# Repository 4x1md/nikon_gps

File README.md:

# DIY GPS Module for Nikon DSLR

The Nikon GPS project is a compact and lightweight DIY module which adds GPS functionality to Nikon DSLR cameras. It adds the ability to record location data for each photo in the EXIF and later view it on a map.

The module is attached to the flash hot shoe mount and connects to the camera's dedicated GPS port. The GPS gets its power from the camera and transmits the received GPS NMEA sentences using UART at 4800 bps. It also features an on/off button and a LED indicator which shows when the GPS module is active.

The project was created mostly to advance my DIY and electronics skills.

## Overview

The idea of building a GPS for my Nikon DSLR me after building the [GPS module for my Yaesu VX-8DE transceiver](https://github.com/4x1md/vx8_gps). I searched the internet and found some projects, some of which had a very small size. For my project I chose RG1411 GPS module which is only 10x10mm in size. It requires 3.3V which can be supplied by the camera.

The first version of the GPS had a linear voltage regulator powering the GPS module. This solution had one big disadvantage: the GPS module was turned off completely and didn't keep any GPS data while it was off. Each time the module was turned on it had to acquire all the required GPS data again and consumed more current during the first minutes after power on. The delay of 3-5 minutes and even more made this GPS module impractical while walking in a city when I turned it on and off very often in order to save camera's battery.

The second version of this GPS project had the following changes:

1. The linear voltage regulator was replaced with a switching power supply with a very high efficiency at low currents.

2. On/off button puts the GPS module is a sleep mode instead of turning it off. In this mode it keeps the GPS data all the time when the GPS is connected to the camera and its start time is much shorter than during a full power-on cycle.

This document describes the latest version of this project. The first version of this project (revision A) is presented in [revision-a.md](docs/revision-a.md).

## Circuit Diagram

The project has the following circuits: GPS module, power supply, on/off switch, logic level shifter and LEDs. All the circuits are assembled on the same PCB.

1. **GPS module.** Hornet ORG1411 was chosen due to its small footprint and good performance. It is powered from the 3.3V supply and is connected in UART mode.

2. **Power supply.** TI TPS62203DBVR is a switching voltage regulator with fixed 3.3V output. It requires only an inductor and filter capacitors in order to work. It features more than 90% at the currents below 1mA. Such efficiency is important for reducing power consumption from the camera.

3. **On/off button.** The button is used to toggle the ON_OFF pin of the GPS for putting it into sleep mode or waking it up. The button is debounced by an RC-filter with a Schmitt trigger.

4. **Logic level shifter.** The logic level shifting circuit converts the 1.8V logic levels of the GPS to 3.3V levels required by the camera. When the GPS is in the sleep mode the level shifter enters high-Z mode. The enable pin of U3 is controlled by a circuit which acts like a flip-flop. If the WAKEUP pin of the GPS is LOW, the output of the AND gate U2 is also LOW and the output of U3 is disabled. After the GPS wakes up, its WAKEUP pin becomes HIGH, but the second input of U2 is still LOW, and its output continues LOW. When the UART TX of the GPS wakes up and becomes HIGH it toggles the output of U2 to HIGH. R5 pulls the B input of the AND gate up and the diode D1 prevents level of the B input from being changed to LOW by the UART RX when the latter transmits zero bits. The output of U2 will remain HIGH until the WAKEUP line falls to LOW again.

6. **LEDs.** The LEDs indicate that the GPS in in active state. They are controlled by the output of U2 and are turned off when the output buffer is in high-Z mode.

## Mechanics

The project is enclosed in a plastic box of 36x36x15mm. These boxes are cheap and are widely available on eBay/AliExpress.

## PCB Design

The PCB was designed in KiCAD. Its shape fits the plastic box shown above.

### 3D Model

### Manufactured PCB

## Assembled Device

## Device Tests

### Design Validation Tests

The tests were done in order to verify the assembled circuit. Refer to [development-tests-rev-b.md](docs/development-tests-rev-b.md) for test notes.

### ORG1411 GPS Module On/Off Tests

The on/off sequence of the ORG1411 GPS module was tested in order to understand how to connect an external on/off button to the module. Refer to [gps-on-off-tests.md](docs/gps-on-off-tests.md) for details.

### Field Tests

## Conclusions

The second version of the module works as I expected. I tested it in Tel Aviv, Budapest and Thessaloniki and it showed fast data acquisition and good precision. Currently, I'm not planning to develop it further.

## Links

### Reference projects

1. [A low-cost GPS module for Nikon DSLRs](https://github.com/marmat/nikon-gp1-diy) by Martin Matysiak
2. [Build Notes for DIY Nikon GPS](http://www.petermillerphoto.com/nikongps/nikongps2.html) by Peter Miller

### Technical data

1. [Nikon D90, D3100, D3200, D5000, D7000 focus / shutter MC-DC2 connector pinout](http://pinoutguide.com/DigitalCameras/nikon_d90_pinout.shtml)

## Questions? Suggestions?
You are more than welcome to contact me with any questions, suggestions or propositions regarding this project. You can:

1. Visit [my QRZ.COM page](https://www.qrz.com/db/4X5DM)
2. Visit [my Facebook profile](https://www.facebook.com/Dima.Meln)
3. Write me an email to iosaaris =at= gmail dot com

## How to Support or Say Thanks

If you like this project, or found here some useful information and want to say thanks, or encourage me to do more, you can buy me a coffee!

You can aslo make a donation with PayPal:

---

**73 de 4X1MD**

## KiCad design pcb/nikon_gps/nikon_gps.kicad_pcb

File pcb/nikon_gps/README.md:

# nikon_gps

This directory stores the latest version of the project. Currently, revision B of the PCB developped in KiCAD 5.1.

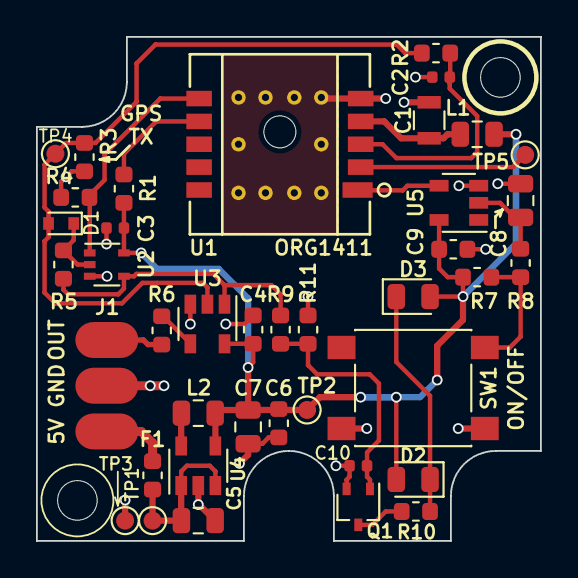
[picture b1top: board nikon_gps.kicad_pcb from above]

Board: 2 copper layers, 28.0 x 28.0 mm, 42 parts (0 on the bottom side), 21 nets.

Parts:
C1: 100nF; C_0805_NarrowPads
C2: 18pF; C_0402
C3, C10: 100nF; C_0402
C4, C9: 100nF; C_0603
C5: 4.7uF; C_0805
C6: 1nF; C_0603
C7: 10uF; C_0805
C8: 100nF; C_0805
D1: Shottky; D_SOD-523
D2, D3: Green; LED_0805
F1: 0.1A; Fuse_0603
J1: 1x03 pads; Connection_Pads_03
L1: 600Ohm; L_0805
L2: 10uH; L_0805
MH1, MH2: M2 screw; MountingHole_2.2mm_M2_DIN965
Q1: NMOS; SOT-323_SC-70
R1, R3, R4: 10K; R_0603
R2, R6: 33; R_0603
R5: 22K; R_0603
R7, R9: 33K; R_0603
R8: 4.7K; R_0603
R10: 330; R_0603
R11: 100K; R_0603
SW1: ON/OFF; SW_SPST_PTS645_4pin
TP1: 5V; Measurement_Point_Round-SMD-Pad_Small
TP2: 3.3V; Measurement_Point_Round-SMD-Pad_Small
TP3: GND; Measurement_Point_Round-SMD-Pad_Small
TP4: GPS TX; Measurement_Point_Round-SMD-Pad_Small
TP5: 1PPS; Measurement_Point_Round-SMD-Pad_Small
U1: Hornet ORG1411; ORG1411_GPS_ALT
U2: 74AUP1T08; SOT-353_SC-70-5
U3: SN74LV1T126; SOT-23-5
U4: TPS62203DBV; SOT-23-5
U5: 74LVC1G14; SOT-23-5

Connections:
+3V3: C3.2, C4.2, C6.1, C7.1, C9.1, D2.2, D3.2, L1.2, L2.2, R1.1, R7.2, TP2.1, U2.5, U3.5, U4.4, U5.5
+5V: C5.1, F1.1, TP1.1, U4.1, U4.3
/1PPS: TP5.1, U1.2
/3.3V_GPS: C1.2, L1.1, U1.4
/5V_IN: F1.2, J1.1
/BUFFER_IN: D1.2, R2.2, R3.2, TP4.1, U3.2
/BUF_OUT: R6.1, U3.4
/GPS_TX: C2.1, R2.1, U1.3
/OE: R5.2, R9.2, U2.4, U3.1
/ON_OFF: U1.1, U5.4
/ON_SW: R7.1, R8.1, SW1.1
/OUT: J1.3, R6.2
/WAKEUP: R4.1, U1.6, U2.1
/~CTS: R1.2, U1.7
GND: C1.1, C2.2, C3.1, C4.1, C5.2, C6.2, C7.2, C8.2, C9.2, C10.2, J1.2, Q1.2, R3.1, R4.2, R11.1, SW1.3, SW1.4, TP3.1, U1.5, U2.3, U3.3, U4.2, U5.3
unnamed: C8.1, R8.2, U5.2
unnamed: C10.1, Q1.1, R9.1, R11.2
unnamed: D1.1, R5.1, U2.2
unnamed: D2.1, D3.1, R10.2
unnamed: L2.1, U4.5
unnamed: Q1.3, R10.1

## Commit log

2019-02-02 KiCAD files and DXF.
2019-05-04 Readme and schematics update.
2019-05-04 Tests report template.
2019-05-04 Development tests without the GPS module.
2019-05-04 Development tests report.
2019-05-04 Schematics.
2019-05-04 Description update.
2019-08-31 Renamed pcb/nikon_gps directory to nikon_gps.kicad4 for creating a backup of the KiCAD 4.x version.
2019-08-31 KiCAD 5.1 version of the revision A.
2020-04-15 LTspice simulations.
2020-04-15 Added photos of the device.
2020-04-15 Added field tests images.
2020-06-05 1. Added GPS module on/off tests. 2. Changed folder and file names.
2020-06-05 File name change.
2020-07-07 Parts choice notes.
2020-08-01 Final version of revision B.
2020-08-09 Update.
2020-09-02 Production files and BOM.
2021-01-23 1. PCB update. 2. Updated 3D model images.
2021-07-03 Revision B tests notes.
2021-07-03 Updae
